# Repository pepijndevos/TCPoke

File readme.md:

# TCPoke

Internet of Pokemon

## Overview

This is what you call full-stack development.

* `tcpoke_shield` KiCAD drawings for a Teensy 2.0 shield for a Game Link Cable.
* `tcpoke_teensy` Arduino sketch for talking to a Game Boy via a Teensy in raw HID mode.
* `tcpoke_chrome` Chrome App talking USB HID and WebRTC.
* `tcpoke_server` Clojure WebSocket server for chat and WebRTC initiation.

## Useful commands

Start the server

    lein run 3000

Deploy server to Heroku

    git subtree push --prefix tcpoke_server heroku master

Compile JSX

    jsx --watch jsx/ .

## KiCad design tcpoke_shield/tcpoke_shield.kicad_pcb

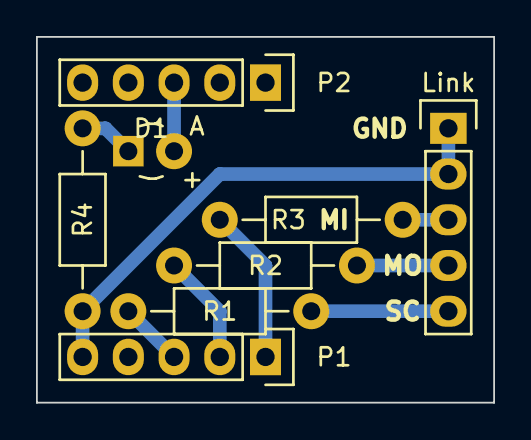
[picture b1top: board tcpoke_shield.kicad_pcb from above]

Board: 2 copper layers, 25.4 x 20.3 mm, 8 parts (0 on the bottom side), 9 nets.

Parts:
D1: LED; Diode_LED_3mm_round_vertical
Link: CONN_01X05; Socket_Strip_Straight_1x05
P1, P2: CONN_01X05; Socket_Strip_Straight_1x05
R1, R2, R3, R4: 1K; Resistor_Horizontal_RM10mm

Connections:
unnamed: D1.1, P2.3
unnamed: D1.2, R4.1
unnamed: Link.1, Link.2, P1.5, R4.2
unnamed: Link.3, R3.2
unnamed: Link.4, R2.2
unnamed: Link.5, R1.2
unnamed: P1.1, R3.1
unnamed: P1.2, R2.1
unnamed: P1.3, R1.1

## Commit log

2015-02-20 try interacting with bgb
2015-02-20 intitial RAW HID code
2015-02-21 bgb seems to be a dead end
2015-02-21 echo over USB works, if within 100ms
2015-02-21 always read
2015-02-21 tcp test
2015-02-21 soft reset
2015-02-22 emulator still acting weird
2015-02-22 Chrome app
2015-02-22 WebRTC test
2015-02-22 First LAN WebRTC trade is a fact
2015-02-24 essetial cosmetic changes
2015-02-25 works on Teensy 2
2015-02-26 shield PCB
2015-02-26 Bower + React WIP
2015-02-26 server WIP
2015-02-27 basic chat working
2015-02-27 support Gen II games
2015-02-27 add LED to shield
2015-02-27 Aleph initiator
2015-02-27 a little more complete chat
2015-02-28 cosmetic changes
2015-02-28 almost working WebRTC code
2015-02-28 working data channel
2015-03-01 heroku
2015-03-01 readme
2015-03-01 Sketch also works for Teensy 3, shield does not
2015-03-01 massive refactor and extend
2015-03-02 trade works again
2015-03-02 add awesome status box
2015-03-02 go away jquery and peerjs, I don't need you
2015-03-05 important change
2015-03-12 icon and deps
2015-03-13 reset button
2015-03-13 Create gh-pages branch via GitHub
2015-03-13 add images
2015-03-13 Add additional requirements
2015-03-15 zero out random data
2015-03-27 add led
2015-03-31 Actual Tindie link
2015-04-01 add video
2015-04-02 try to prevent double reads, not really working
2015-04-02 don't overwrite usb thing
2015-04-03 New video
2015-04-06 bump version
2015-04-06 send users on connect
2015-04-09 broken attempt at bgb support
2015-04-12 fix fighting, maybe
2015-04-12 version bump
